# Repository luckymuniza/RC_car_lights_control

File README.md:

# RC Car Lights Control

Lighting controller for a large-scale RC truck. An RP2040 board sits between the
FlySky receiver and a **MFC-03** multi-function unit, reads the receiver's **iBUS**
stream directly, and drives the vehicle's LED lighting from it — while still letting the
MFC-03 keep control of the things it does best (sound, engine start-up sequence,
turn-signal timing, brake detection).

The MCU is both a *consumer* of the MFC-03 (it watches the MFC's own light and
turn-signal outputs) and a *producer* for it (it synthesises a servo signal into the MFC's
light channel so the MFC's internal "lights on" state stays in sync).

```
FlySky FS-i6X  ──2.4GHz──►  FS-iA6B RX ──┬── iBUS (UART, 115200) ──► RP2040 ──► LED outputs
                                          │                            ▲  │
                                          └── (channels) ──► MFC-03 ───┘  │
                                                                ▲          │
                                                                └──────────┘
                                                            synthesised servo signal
```

## Repository layout

| Path | Contents |
| --- | --- |
| `FW/` | Firmware — C, Raspberry Pi Pico SDK ≥ 2.1.0 |
| `HW/rccarcontrol/` | KiCad 9 project: schematic, PCB, gerbers, DRC report |
| `doc/` | MFC-03 manual, FS-i6X manual, output mapping spreadsheet, wiring manual |
| `sim/` | Multisim analog simulation (`Design1.ms14`) |

## Hardware

The board is built around a **USB-C RP2040 "Pico C" module** (`HW/.../rccarcontrol.kicad_sch`,
symbol `Pico_type_c`). Note this is *not* pin-compatible with a genuine Raspberry Pi Pico:
the module breaks out **GPIO29 on pad 35** and **GPIO23 on pad 37**, where a stock Pico has
`ADC_VREF` and `3V3_EN`. The firmware drives both of those pins, so it will not run
correctly on a stock Pico without remapping `FRONT_RAMP_LIGHT_OUT_PIN` and
`TURN_R_FRONT_OUT_PIN`.

Interfacing:

- **Inputs from the MFC-03** go through `EL3H7` optocouplers (U2–U8), so they are
  **active-low** and the firmware enables internal pull-ups on all of them.
- **Outputs** drive `IRLML0030` N-MOSFETs. Solder jumpers `JP3`–`JP7` select `+7V2_LED` or
  `+5V_LED` per LED group; `JP1`/`JP2` bring the receiver / external supply onto `+5V`.
- **Reverse light** (`REVERSE_LIGHT_IN`, opto U1) is wired straight to Q1/Q2 in hardware and
  never reaches the MCU — there is intentionally no firmware for it.

### Pin map

Verified against the PCB netlist. "Pad" is the module pad number.

**Outputs**

| GPIO | Pad | Net | Firmware | Type |
| --- | --- | --- | --- | --- |
| 0 | 1 | `LED_POWER` | `lights.c` | digital — master LED supply gate |
| 1 | 2 | `LOW_BEAM_OUT` | `lights.c` | digital |
| 2 | 4 | `HIGH_BEAM_OUT` | `lights.c` | digital |
| 3 | 5 | `FOG_LIGHT_OUT` | `lights.c` | digital |
| 4 | 6 | `AUX_1_OUT` | `aux1.c` | PWM slice 2A, 50 Hz servo, **inverted** polarity |
| 5 | 7 | `AUX_2_OUT` | `main.c` | digital — toggled every loop pass (loop-rate test point) |
| 6 | 9 | `TURN_R_PWM_OUT` | `turn_light.c` | PWM slice 3A, 2 kHz |
| 7 | 10 | `TURN_L_PWM_OUT` | `turn_light.c` | PWM slice 3B, 2 kHz |
| 8 | 11 | `TURN_L_FRONT_OUT` | `turn_light.c` | digital — short front-indicator pulse |
| 9 | 12 | `SEARCH_LIGHT_OUT` | `lights.c` | digital |
| 10 | 14 | `REAR_LIGHT_PWM_OUT` | `rear_light.c` | PWM slice 5A, 500 Hz |
| 11 | 15 | `SIDE_LIGHT_1_OUT` | `lights.c` | digital |
| 12 | 16 | `SIDE_LIGHT_2_OUT` | `lights.c` | digital |
| 13 | 17 | `RX_PWM_OUT` | `to_mfc.c` | PWM slice 6B, 50 Hz servo → MFC light channel |
| 14 | 19 | `BEACON_SMALL_PWM_OUT` | `beacons.c` | PWM slice 7A, 50 Hz servo |
| 15 | 20 | `BEACON_BIG_PWM_OUT` | `beacons.c` | PWM slice 7B, 50 Hz servo |
| 23 | 37 | `TURN_R_FRONT_OUT` | `turn_light.c` | digital |
| 25 | — | on-board LED | `main.c` | boot-blink only |
| 27 | 32 | `DAY_LIGHT_OUT` | `lights.c` | digital — on permanently after init |
| 28 | 34 | `POSITION_LIGHT_OUT` | `lights.c` | digital |
| 29 | 35 | `FRONT_RAMP_OUT` | `lights.c` | digital |

**Inputs** (all pulled up, active low)

| GPIO | Pad | Net | Firmware | Purpose |
| --- | --- | --- | --- | --- |
| 16 | 21 | `TURN_R_IN` | `turn_light.c` | MFC right indicator |
| 17 | 22 | `LIGHT_0_IN` | `lights.c` | configured, **not read** |
| 18 | 24 | `LIGHT_1_IN` | `lights.c` | MFC light state + start-up flash pattern |
| 19 | 25 | `LIGHT_2_IN` | `lights.c` | configured, **not read** |
| 20 | 26 | `LIGHT_3_IN` | `lights.c` | configured, **not read** |
| 21 | 27 | `RX_SBUS_IN` | `ibus.c` | UART1 RX — iBUS, 115200 8N1 |
| 22 | 29 | `TURN_L_IN` | `turn_light.c` | MFC left indicator |
| 26 | 31 | `REAR_BRAKE_IN` | `rear_light.c` | ADC0 — MFC rear/brake light level |

### Transmitter channel map

From `FW/ibus.h` (`ibus_channel`), 1-based as shown on the FS-i6X:

| Ch | Name | Used by |
| --- | --- | --- |
| 1 | Steering | — (passes to MFC directly) |
| 2 | MFC light channel | `to_mfc.c`, `aux1.c` |
| 3 | Throttle | — |
| 4 | Throttle X | — |
| 5 | Mode switch | `aux1.c` |
| 6 | Beacon switch | `beacons.c` |
| 7 | Gear switch | — |
| 8 | Light switch | `lights.c` |
| 9 / 10 | Pot A / Pot B | — |

Channels 1, 3, 4, 7 and the pots are declared but not consumed by the firmware.

## Firmware

### Structure

Cooperative, non-blocking super-loop. Every module exposes `*_init()` (called once) and
`*_service()` (called every pass, returns immediately). No RTOS, no blocking delays after
start-up, no dynamic allocation. All timing uses `time_us_32()` deadlines compared as
signed differences, so 32-bit wrap is handled correctly.

| Module | Responsibility |
| --- | --- |
| `main.c` | Boot blink, init order, super-loop |
| `ibus.c` | iBUS frame decoding — the only interrupt-driven part |
| `lights.c` | Light-state machine, side lights, MFC light-state sync, start-up flash replay |
| `turn_light.c` | Indicator soft fade-in / fade-out driven by MFC edges |
| `rear_light.c` | Tail / brake light PWM, ADC brake detection |
| `beacons.c` | Rotating beacons, fog + search light, beacon configuration mode |
| `to_mfc.c` | Synthesised servo output back into the MFC light channel |
| `aux1.c` | Diverts the light channel to an auxiliary servo output (crane) |
| `switch.h` | Shared 3-position-switch state machine constants |

### iBUS decoder

`ibus.c` decodes the standard 32-byte FlySky iBUS servo frame:

```
0x20 0x40 <14 × uint16 LE channel values> <uint16 LE checksum>
```

The checksum is validated by summing all 32 bytes and requiring `0xFFFF`. Frame
synchronisation is done by **inter-byte gap**, not by header alone: a byte arriving more
than `SBUS_NEXT_FRAME_TIMEGAP` (3 ms) after the previous one is treated as a frame start.
Frames arrive roughly every 7 ms and each takes ~2.7 ms, so the gap is unambiguous.

The ISR writes into `channel_data`; `ibus_service()` copies it to `channel_data_saved`
with interrupts disabled, and `ibus_get_channel()` reads only the snapshot.

### Light state machine (`lights.c`)

Channel 8 acts as a momentary 3-position switch. Short pull **up** steps forward, holding
up for >1 s steps back:

```
OFF ──► POSITION ──► LOW_BEAM ──► HIGH_BEAM ──► RAMP
    ◄──          ◄──          ◄──           ◄──          (hold >1 s)
```

Pushing **down** flashes the front ramp light for as long as it is held.

Side lights (`SIDE_LIGHT_1/2`) have their own state: off, on with the position lights, a
double-flash alternating beacon pattern (when the rotating beacons are on), or a slow
0.5 s blink to indicate beacon-configuration mode.

### MFC light-state sync

The MFC-03 beeps when the engine is switched off with its lights still on, so its internal
state must track the real one. `update_lights_in_mfc()` compares `l_state` against
`LIGHT_1_IN` and, when they disagree, asks `to_mfc.c` to emit one 100 ms pulse train on the
synthesised light channel — the equivalent of one stick flick. It repeats every 0.5 s until
the states match.

### Start-up flash replay

On engine start the MFC-03 flashes its light output rapidly. `detect_starting_seq()`
detects this (edges closer than 25 ms apart), records the on/off durations into a 64-entry
ring buffer — duration in bits 0–14, level in bit 15 — and replays them onto `LED_POWER`
so the real headlights flicker in step with the MFC's simulated start-up. While the replay
is active, MFC light-state sync is suspended.

### Turn signals

The MFC drives the blink timing; the firmware only reshapes it. On each falling edge of
`TURN_L_IN` / `TURN_R_IN` it pulses the front indicator hard for 100 ms and simultaneously
ramps the PWM channel up (100 counts / 10 ms), holds at full for 100 ms, then ramps down
(50 counts / 7.5 ms) — roughly a 600 ms incandescent-style fade. Re-triggering is ignored
while a fade is still running.

### Rear / brake light

`REAR_BRAKE_IN` is sampled on ADC0 through a 32-sample moving average. Below
`REAR_LIGHT_BRAKE_LEVEL` the tail light PWM goes to full (brake); otherwise it follows the
main light state at 25 % duty, or off.

### Beacons

Two servo-protocol beacon outputs, driven as if by a stick:

- **Short pull up** — both beacons on, side lights switch to the alternating flash pattern.
- **Hold up >1 s** — both off. The small beacon has to be cycled through all four of its
  internal modes to reach off, which `beacon_small_off()` does with eight 50 ms pulses.
- **Hold up >5 s** — enter configuration mode: big beacon on, side lights blink slowly. In
  config, short up = next mode, short down = next brightness, hold up >5 s = exit.
- **Short pull down** — cycles the rear search light and the fog light. Hold down >1 s
  turns both off. The fog light only comes on if the main lights are on.

### Auxiliary output

When channel 5 is above 1800, `aux1.c` mirrors the channel-2 value onto `AUX_1_OUT`
(inverted polarity) for a crane servo, and tells `to_mfc.c` to park the MFC light channel at
centre so the MFC ignores it.

## Building

Requires the Raspberry Pi Pico SDK **2.1.0 or later**, `arm-none-eabi-gcc`, CMake ≥ 3.12
and `picotool`.

```sh
export PICO_SDK_PATH=/path/to/pico-sdk
cd FW
cmake -B build -DCMAKE_BUILD_TYPE=Debug
cmake --build build
```

Output is `build/car_lighting.uf2` (plus `.elf`, `.bin`, `.hex`, `.map`). The build prints
memory usage and a section size summary.

`CMakeLists.txt` hardcodes `picotool_DIR` to a local absolute path; override it with
`-Dpicotool_DIR=...` or edit it if picotool lives elsewhere. `stdio` over both USB and UART
is disabled — GPIO0/GPIO1 are used as light outputs, so UART0 is unavailable. To get printf
debugging you must free those pins first.

## Flashing

Hold `BOOTSEL` while plugging the board in and copy the `.uf2` to the `RPI-RP2` drive.

`FW/up.bat` automates this on Windows: it pokes the USB CDC port at 1200 baud to force the
board into BOOTSEL, finds the `RPI-RP2` volume and copies the image. It references helper
tools under `f:\_Work\_Programing\rpi\` and expects the artefact in
`cmake-build-debug-system-arm\`, so the paths need adjusting for the current build
directory before it will work.

## Known limitations

- **No receiver failsafe.** `ibus_get_channel()` returns the last valid frame forever. If
  the link drops, the lighting freezes in its last state and the synthesised MFC channel
  keeps repeating a stale value.
- **Boot blocks on iBUS.** `main()` spins in `while (!ibus_data_valid())` before any
  outputs are initialised, so with no receiver signal the board never leaves start-up.
- **No watchdog.**
- `LIGHT_0_IN`, `LIGHT_2_IN`, `LIGHT_3_IN` are wired and configured but unused.

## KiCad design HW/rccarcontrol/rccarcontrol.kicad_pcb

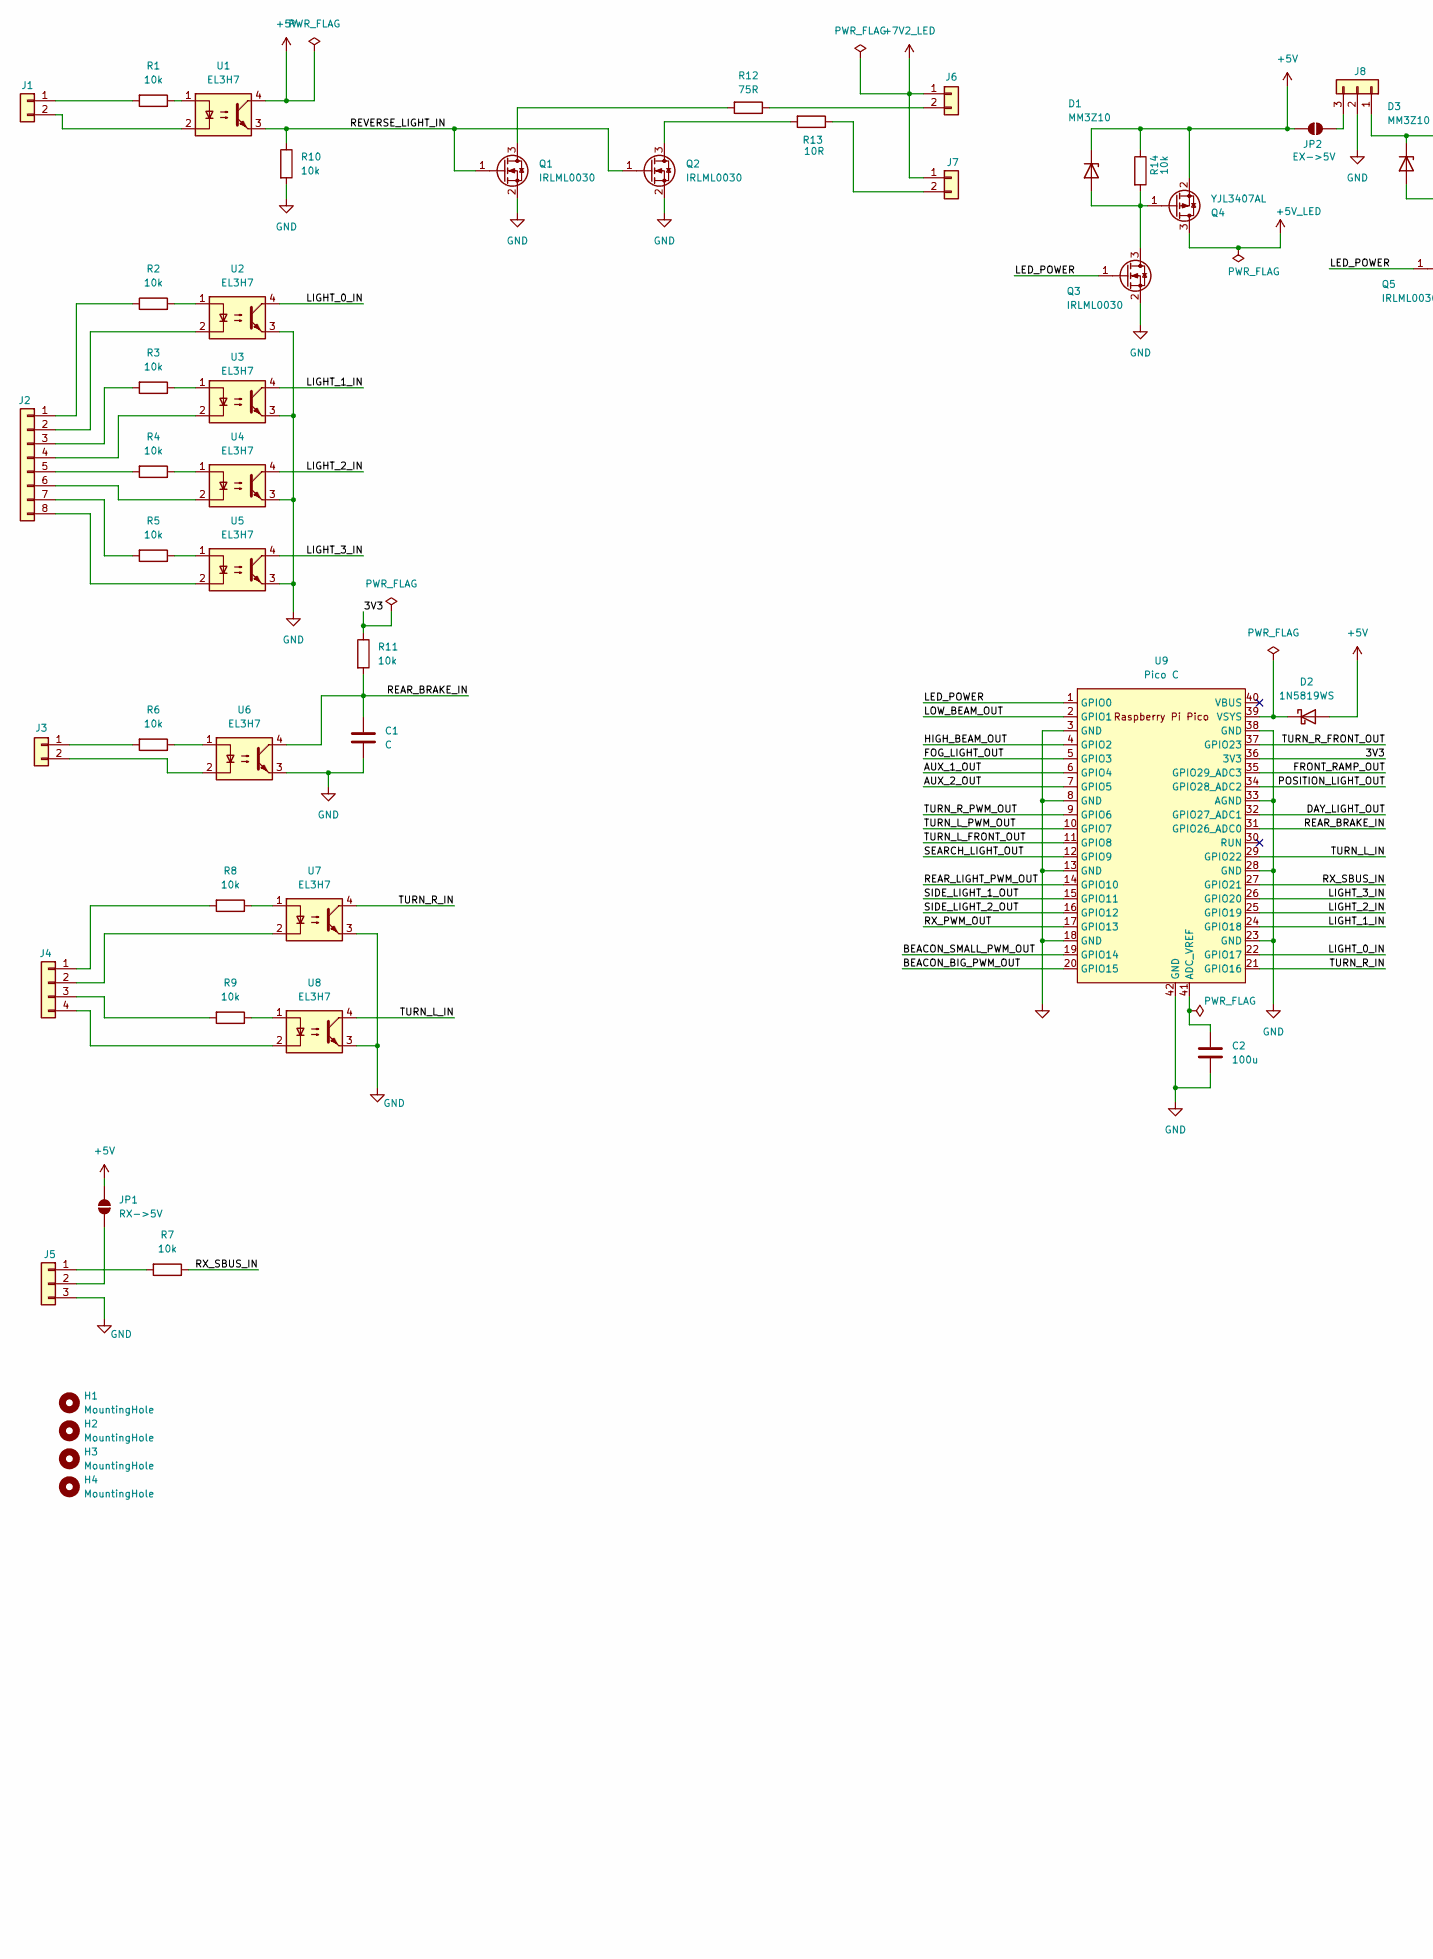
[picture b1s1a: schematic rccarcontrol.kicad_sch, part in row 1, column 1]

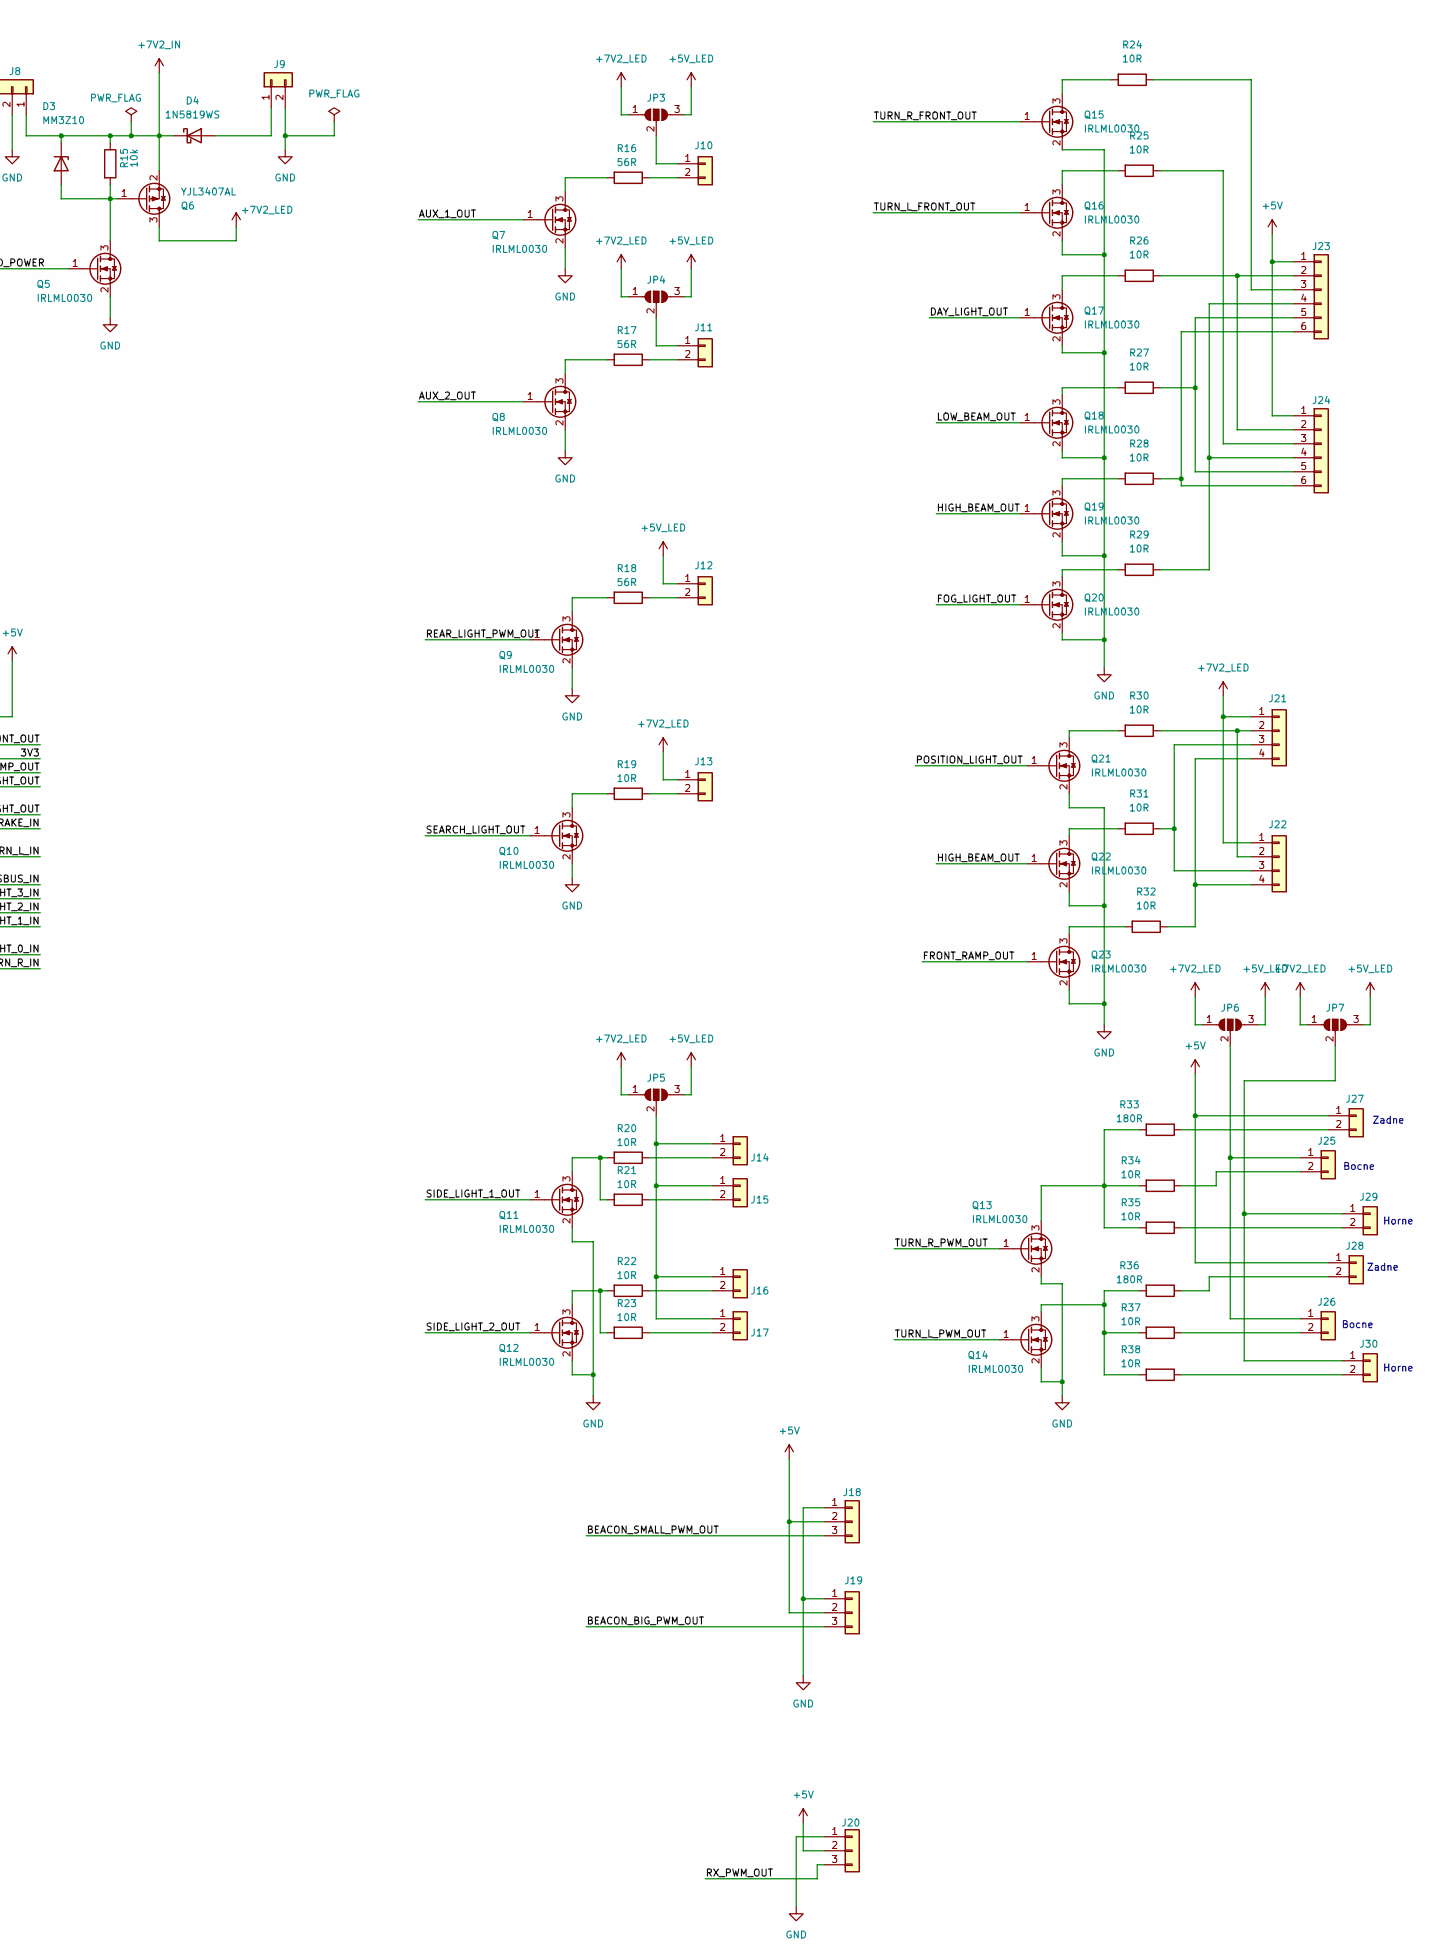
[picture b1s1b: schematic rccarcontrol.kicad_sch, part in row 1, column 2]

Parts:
C1: C; C_1206_3216Metric_Pad1.33x1.80mm_HandSolder
C2: 100u; C_1206_3216Metric_Pad1.33x1.80mm_HandSolder
D1, D3: MM3Z10; D_SOD-323F
D2, D4: 1N5819WS; D_SOD-123
H1, H2, H3, H4: MountingHole; MountingHole_2mm
J1, J3, J6, J7, J9, J10, J11, J12, J13, J14, J15, J16, J17, J25, J26, J27, J28, J29, J30: Conn_01x02; JST_PH_B2B-PH-K_1x02_P2.00mm_Vertical
J2: Conn_01x08; JST_PH_B8B-PH-K_1x08_P2.00mm_Vertical
J4, J21, J22: Conn_01x04; JST_PH_B4B-PH-K_1x04_P2.00mm_Vertical
J5, J8, J18, J19, J20: Conn_01x03; JST_PH_B3B-PH-K_1x03_P2.00mm_Vertical
J23, J24: Conn_01x06; JST_PH_B6B-PH-K_1x06_P2.00mm_Vertical
JP1: RX->5V; SolderJumper-2_P1.3mm_Open_RoundedPad1.0x1.5mm
JP2: EX->5V; SolderJumper-2_P1.3mm_Open_RoundedPad1.0x1.5mm
JP3, JP4, JP5, JP6, JP7: SolderJumper_3_Open; SolderJumper-3_P1.3mm_Open_RoundedPad1.0x1.5mm_NumberLabels
Q1, Q2, Q3, Q5, Q7, Q8, Q9, Q10, Q11, Q12, Q13, Q14, Q15, Q16, Q17, Q18, Q19, Q20, Q21, Q22, Q23: IRLML0030; SOT-23-3
Q4, Q6: YJL3407AL; SOT-23-3
R1, R2, R3, R4, R5, R6, R7, R8, R9, R10, R11, R14, R15: 10k; R_0805_2012Metric_Pad1.20x1.40mm_HandSolder
R12: 75R; R_0805_2012Metric_Pad1.20x1.40mm_HandSolder
R13, R19, R20, R21, R22, R23, R24, R25, R26, R27, R28, R29, R30, R31, R32, R34, R35, R37, R38: 10R; R_0805_2012Metric_Pad1.20x1.40mm_HandSolder
R16, R17, R18: 56R; R_0805_2012Metric_Pad1.20x1.40mm_HandSolder
R33, R36: 180R; R_0805_2012Metric_Pad1.20x1.40mm_HandSolder
U1, U2, U3, U4, U5, U6, U7, U8: EL3H7; SOP-4_4.4x2.6mm_P1.27mm
U9: Pico C; RPi_Pico_type_c_SMD_TH

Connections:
+5V: D1.1 (K), D2.2 (A), J18.2, J19.2, J20.2, J23.1, J24.1, J27.1, J28.1, JP1.2 (B), JP2.2 (B), Q4.2 (S), R14.1, U1.4
+5V_LED: J12.1, JP3.3 (B), JP4.3 (B), JP5.3 (B), JP6.3 (B), JP7.3 (B), Q4.3 (D)
+7V2_IN: D3.1 (K), D4.1 (K), J8.1, Q6.2 (S), R15.1
+7V2_LED: J6.1, J7.1, J13.1, J21.1, J22.1, JP3.1 (A), JP4.1 (A), JP5.1 (A), JP6.1 (A), JP7.1 (A), Q6.3 (D)
/3V3: R11.1, U9.36 (3V3)
/AUX_1_OUT: Q7.1 (G), U9.6 (GPIO4)
/AUX_2_OUT: Q8.1 (G), U9.7 (GPIO5)
/BEACON_BIG_PWM_OUT: J19.3, U9.20 (GPIO15)
/BEACON_SMALL_PWM_OUT: J18.3, U9.19 (GPIO14)
/DAY_LIGHT_OUT: Q17.1 (G), U9.32 (GPIO27_ADC1)
/FOG_LIGHT_OUT: Q20.1 (G), U9.5 (GPIO3)
/FRONT_RAMP_OUT: Q23.1 (G), U9.35 (GPIO29_ADC3)
/HIGH_BEAM_OUT: Q19.1 (G), Q22.1 (G), U9.4 (GPIO2)
/LED_POWER: Q3.1 (G), Q5.1 (G), U9.1 (GPIO0)
/LIGHT_0_IN: U2.4, U9.22 (GPIO17)
/LIGHT_1_IN: U3.4, U9.24 (GPIO18)
/LIGHT_2_IN: U4.4, U9.25 (GPIO19)
/LIGHT_3_IN: U5.4, U9.26 (GPIO20)
/LOW_BEAM_OUT: Q18.1 (G), U9.2 (GPIO1)
/POSITION_LIGHT_OUT: Q21.1 (G), U9.34 (GPIO28_ADC2)
/REAR_BRAKE_IN: C1.2, R11.2, U6.4, U9.31 (GPIO26_ADC0)
/REAR_LIGHT_PWM_OUT: Q9.1 (G), U9.14 (GPIO10)
/REVERSE_LIGHT_IN: Q1.1 (G), Q2.1 (G), R10.1, U1.3
/RX_PWM_OUT: J20.3, U9.17 (GPIO13)
/RX_SBUS_IN: R7.1, U9.27 (GPIO21)
/SEARCH_LIGHT_OUT: Q10.1 (G), U9.12 (GPIO9)
/SIDE_LIGHT_1_OUT: Q11.1 (G), U9.15 (GPIO11)
/SIDE_LIGHT_2_OUT: Q12.1 (G), U9.16 (GPIO12)
/TURN_L_FRONT_OUT: Q16.1 (G), U9.11 (GPIO8)
/TURN_L_IN: U8.4, U9.29 (GPIO22)
/TURN_L_PWM_OUT: Q14.1 (G), U9.10 (GPIO7)
/TURN_R_FRONT_OUT: Q15.1 (G), U9.37 (GPIO23)
/TURN_R_IN: U7.4, U9.21 (GPIO16)
/TURN_R_PWM_OUT: Q13.1 (G), U9.9 (GPIO6)
GND: C1.1, C2.1, J5.3, J8.2, J9.2, J18.1, J19.1, J20.1, Q1.2 (S), Q2.2 (S), Q3.2 (S), Q5.2 (S), Q7.2 (S), Q8.2 (S), Q9.2 (S), Q10.2 (S), Q11.2 (S), Q12.2 (S), Q13.2 (S), Q14.2 (S), Q15.2 (S), Q16.2 (S), Q17.2 (S), Q18.2 (S), Q19.2 (S), Q20.2 (S), Q21.2 (S), Q22.2 (S), Q23.2 (S), R10.2, U2.3, U3.3, U4.3, U5.3, U6.3, U7.3, U8.3, U9.3 (GND), U9.8 (GND), U9.13 (GND), U9.18 (GND), U9.23 (GND), U9.28 (GND), U9.33 (AGND), U9.38 (GND), U9.42 (GND)
unnamed: D1.2 (A), Q3.3 (D), Q4.1 (G), R14.2
unnamed: D2.1 (K), U9.39 (VSYS)
unnamed: D3.2 (A), Q5.3 (D), Q6.1 (G), R15.2
unnamed: D4.2 (A), J9.1
unnamed: J1.1, R1.2
unnamed: J1.2, U1.2
unnamed: J2.1, R2.1
unnamed: J2.2, U2.2
unnamed: J2.3, R3.2
unnamed: J2.4, U3.2
unnamed: J2.5, R4.2
unnamed: J2.6, U4.2
unnamed: J2.7, R5.2
unnamed: J2.8, U5.2
unnamed: J3.1, R6.2
unnamed: J3.2, U6.2
unnamed: J4.1, R8.2
unnamed: J4.2, U7.2
unnamed: J4.3, R9.2
unnamed: J4.4, U8.2
unnamed: J5.1, R7.2
unnamed: J5.2, JP1.1 (A)
unnamed: J6.2, R12.1
unnamed: J7.2, R13.1
unnamed: J8.3, JP2.1 (A)
unnamed: J10.1, JP3.2 (C)
unnamed: J10.2, R16.1
unnamed: J11.1, JP4.2 (C)
unnamed: J11.2, R17.1
unnamed: J12.2, R18.1
unnamed: J13.2, R19.1
unnamed: J14.1, J15.1, J16.1, J17.1, JP5.2 (C)
unnamed: J14.2, R20.1
unnamed: J15.2, R21.1
unnamed: J16.2, R22.1
unnamed: J17.2, R23.1
unnamed: J21.2, J22.2, R30.1
unnamed: J21.3, J22.3, R31.1
unnamed: J21.4, J22.4, R32.1
unnamed: J23.2, J24.2, R26.1
unnamed: J23.3, R24.1
unnamed: J23.4, J24.4, R29.1
unnamed: J23.5, J24.5, R27.1
unnamed: J23.6, J24.6, R28.1
unnamed: J24.3, R25.1
unnamed: J25.1, J26.1, JP6.2 (C)
unnamed: J25.2, R34.1
unnamed: J26.2, R37.1
unnamed: J27.2, R33.1
unnamed: J28.2, R36.1
unnamed: J29.1, J30.1, JP7.2 (C)
unnamed: J29.2, R35.1
unnamed: J30.2, R38.1
unnamed: Q1.3 (D), R12.2
unnamed: Q2.3 (D), R13.2
unnamed: Q7.3 (D), R16.2
unnamed: Q8.3 (D), R17.2
unnamed: Q9.3 (D), R18.2
unnamed: Q10.3 (D), R19.2
unnamed: Q11.3 (D), R20.2, R21.2
unnamed: Q12.3 (D), R22.2, R23.2
unnamed: Q13.3 (D), R33.2, R34.2, R35.2
unnamed: Q14.3 (D), R36.2, R37.2, R38.2
unnamed: Q15.3 (D), R24.2
unnamed: Q16.3 (D), R25.2
unnamed: Q17.3 (D), R26.2
unnamed: Q18.3 (D), R27.2
unnamed: Q19.3 (D), R28.2
unnamed: Q20.3 (D), R29.2
unnamed: Q21.3 (D), R30.2
unnamed: Q22.3 (D), R31.2
unnamed: Q23.3 (D), R32.2
unnamed: R1.1, U1.1
unnamed: R2.2, U2.1
unnamed: R3.1, U3.1
unnamed: R4.1, U4.1
unnamed: R5.1, U5.1
unnamed: R6.1, U6.1
unnamed: R8.1, U7.1
unnamed: R9.1, U8.1
unnamed: C2.2, U9.41 (ADC_VREF)

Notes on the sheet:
Horne
Zadne
Bocne

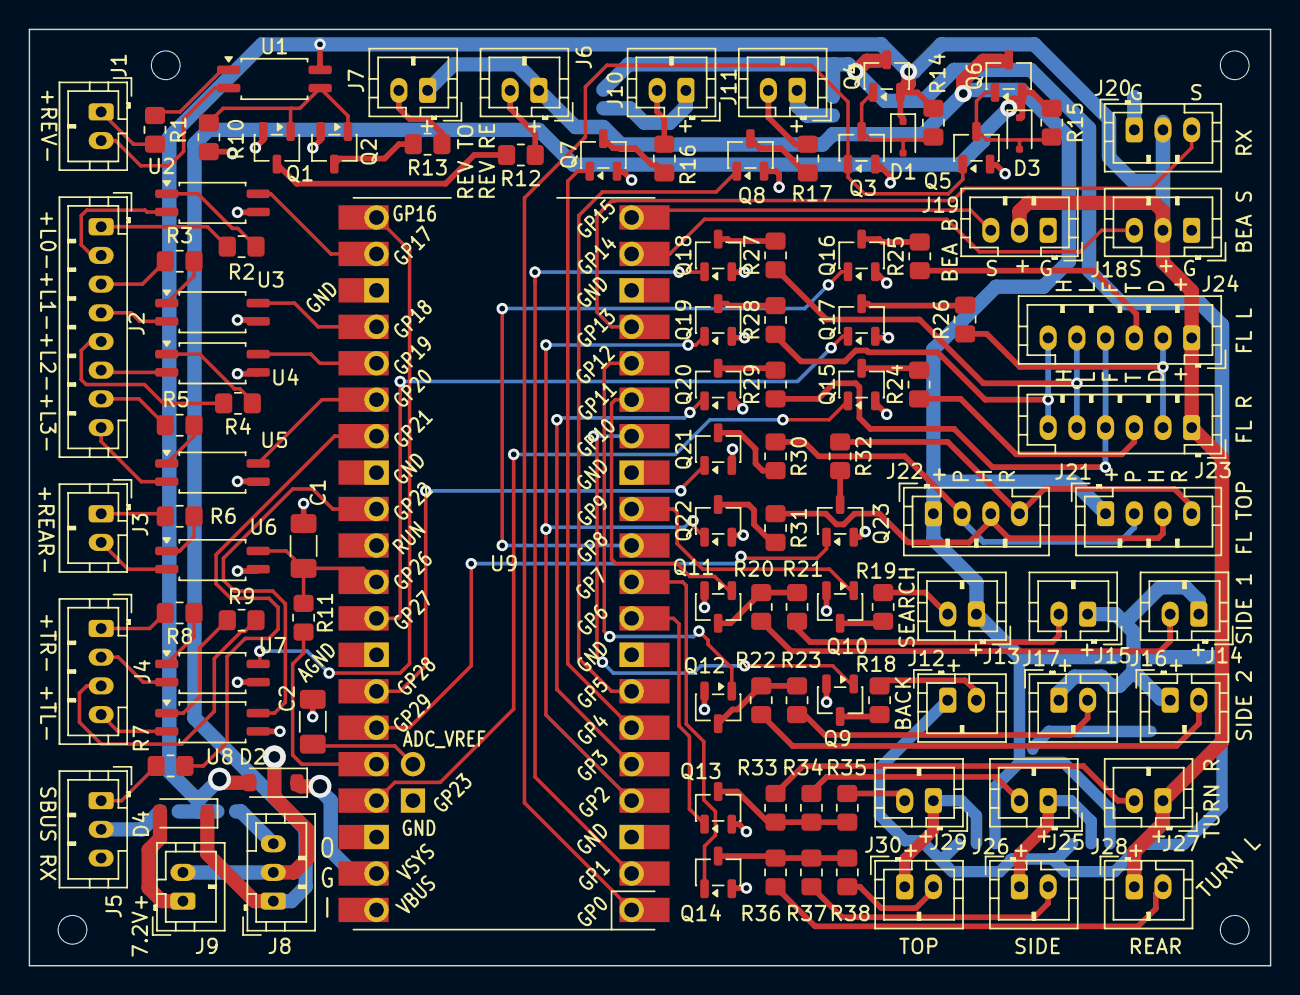
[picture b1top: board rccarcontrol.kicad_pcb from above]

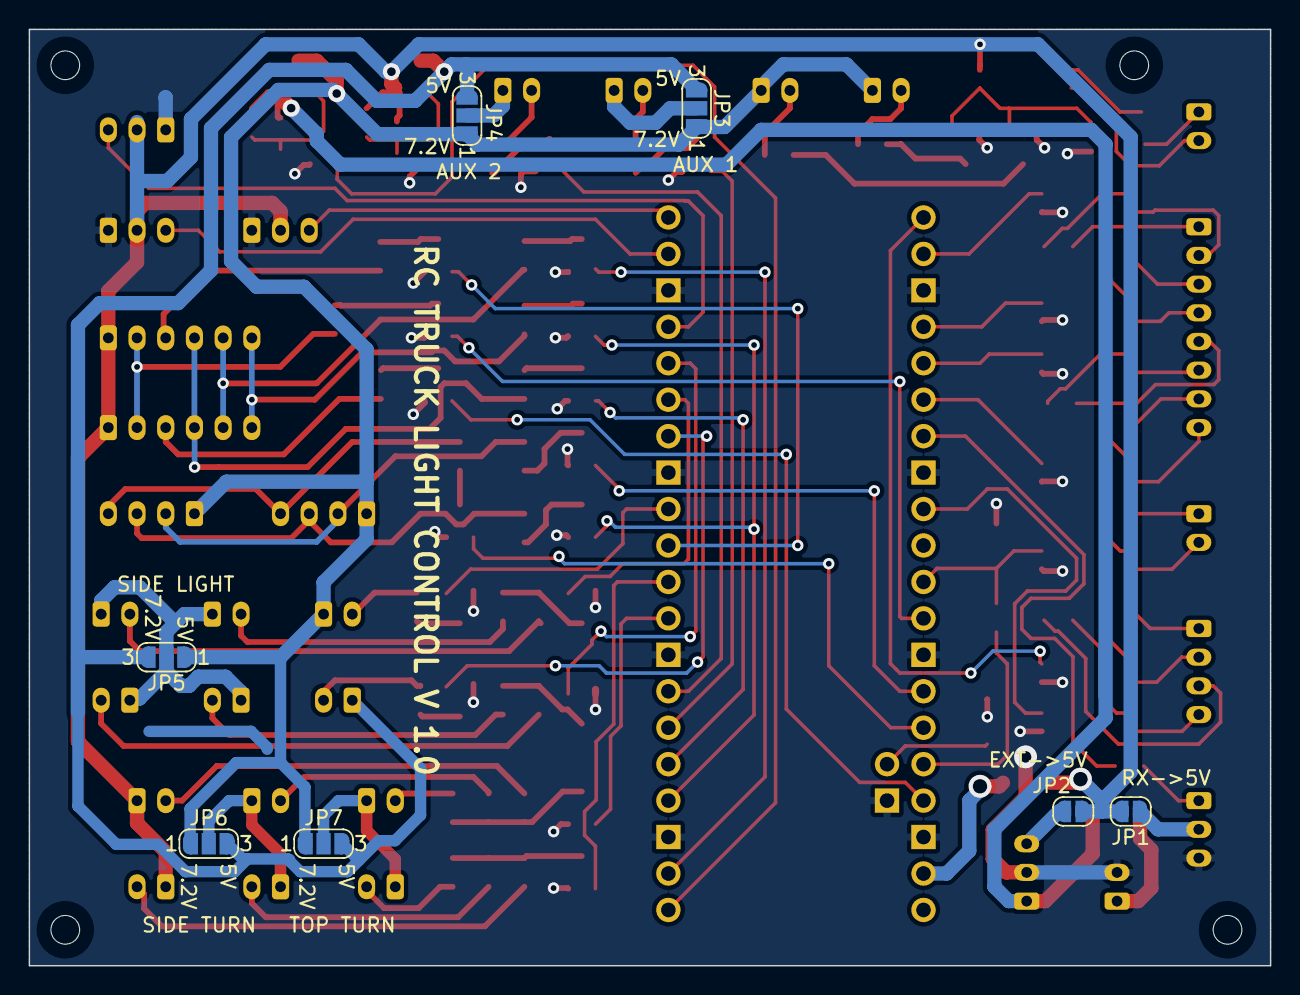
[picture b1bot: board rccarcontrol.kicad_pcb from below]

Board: 2 copper layers, 86.5 x 65.2 mm, 117 parts (7 on the bottom side), 116 nets.

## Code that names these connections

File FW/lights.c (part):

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#include "beacons.h"
#include "to_mfc.h"

#define LED_POWER_PIN 0
#define DAY_LIGHT_OUTPUT_PIN 27  //0 je stdout uart0
#define LOW_BEAM_OUT_PIN    1
#define HIGH_BEAM_OUT_PIN   2
#define FOG_LIGHT_OUT_PIN   3
#define POSITION_LIGHT_OUT_PIN    28
#define FRONT_RAMP_LIGHT_OUT_PIN    29
#define REAR_SEARCH_LIGHT_OUT_PIN 9
#define SIDE_LIGHT_1_OUT_PIN 11
#define SIDE_LIGHT_2_OUT_PIN 12

//pwm out

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static uint8_t starting_seq = 0;

void side_light_1_on (void) {
    gpio_put(SIDE_LIGHT_1_OUT_PIN, 1);
}
void side_light_1_off (void) {
    gpio_put(SIDE_LIGHT_1_OUT_PIN, 0);
}
void side_light_2_on (void) {
    gpio_put(SIDE_LIGHT_2_OUT_PIN, 1);
}
void side_light_2_off (void) {
    gpio_put(SIDE_LIGHT_2_OUT_PIN, 0);
}

void day_light_on (void) {
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}

void low_beam_on (void) {
    gpio_put(LOW_BEAM_OUT_PIN, 1);
}
void low_beam_off (void) {
    gpio_put(LOW_BEAM_OUT_PIN, 0);
}

void high_beam_on (void) {
    gpio_put(HIGH_BEAM_OUT_PIN, 1);
}
void high_beam_off (void) {
    gpio_put(HIGH_BEAM_OUT_PIN, 0);
}

void fog_light_on (void) {
    gpio_put(FOG_LIGHT_OUT_PIN, 1);
}
void fog_light_off (void) {
    gpio_put(FOG_LIGHT_OUT_PIN, 0);
}

void position_light_on (void) {
    gpio_put(POSITION_LIGHT_OUT_PIN, 1);
}
void position_light_off (void) {
    gpio_put(POSITION_LIGHT_OUT_PIN, 0);
}

void front_ramp_light_on (void) {
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    gpio_put(REAR_SEARCH_LIGHT_OUT_PIN, 0);
}

//okrem pinu led_power este aj hlavne svetla lebo tam to 5V nespina
void led_power_on (void) {
    gpio_put(LED_POWER_PIN, 1);
    if (l_state == L_STATE_LOW_BEAM) {
        low_beam_on();
    }
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

void led_power_off (void) {
    gpio_put(LED_POWER_PIN, 0);
    if (l_state == L_STATE_LOW_BEAM) {
        low_beam_off();
    }
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    //init pins
    gpio_set_function_masked(
      (1<<DAY_LIGHT_OUTPUT_PIN)
      |(1<<LED_POWER_PIN)
      |(1<<LOW_BEAM_OUT_PIN)
      |(1<<HIGH_BEAM_OUT_PIN)
      |(1<<FOG_LIGHT_OUT_PIN)
      |(1<<POSITION_LIGHT_OUT_PIN)
      |(1<<FRONT_RAMP_LIGHT_OUT_PIN)
      |(1<<REAR_SEARCH_LIGHT_OUT_PIN)
      |(1<<SIDE_LIGHT_1_OUT_PIN)
      |(1<<SIDE_LIGHT_2_OUT_PIN)
      |(1<<LIGHT_0_17_IN_PIN)
      |(1<<LIGHT_1_15_IN_PIN)
      |(1<<LIGHT_2_20_IN_PIN)
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        |(1<<LIGHT_2_20_IN_PIN)
        |(1<<LIGHT_3_13_IN_PIN));
    gpio_set_dir_out_masked(
    (1<<LED_POWER_PIN)
        |(1<<DAY_LIGHT_OUTPUT_PIN)
        |(1<<LOW_BEAM_OUT_PIN)
        |(1<<HIGH_BEAM_OUT_PIN)
        |(1<<FOG_LIGHT_OUT_PIN)
        |(1<<POSITION_LIGHT_OUT_PIN)
        |(1<<FRONT_RAMP_LIGHT_OUT_PIN)
        |(1<<REAR_SEARCH_LIGHT_OUT_PIN)
        |(1<<SIDE_LIGHT_1_OUT_PIN)
        |(1<<SIDE_LIGHT_2_OUT_PIN));

    //pullups
    gpio_set_pulls(LIGHT_0_17_IN_PIN,true,false);
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
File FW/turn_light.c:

//
// Created by all on 26. 11. 2025.
//

#include "turn_light.h"
#include "pico/stdlib.h"
#include "hardware/pwm.h"



#define TURN_L_FRONT_OUT_PIN 8   //predne smerovky pre kratky pulz
#define TURN_R_FRONT_OUT_PIN 23   //predne smerovky pre kratky pulz
#define TURN_R_PWM_OUT_PIN   6          //slice 3 A
#define TURN_L_PWM_OUT_PIN   7          //slice 3 B

#define TURN_LIGHT_R_21_IN_PIN 16
#define TURN_LIGHT_L_22_IN_PIN 22

#define TURN_LIGHT_R_MASK (1<<TURN_LIGHT_R_21_IN_PIN)
#define TURN_LIGHT_L_MASK (1<<TURN_LIGHT_L_22_IN_PIN)

#define TURN_LIGHT_PWM_INCREMENT 100
#define TURN_LIGHT_PWM_DECREMENT 50

#define TURN_LIGHT_INC_TIME_US 10000 //us
#define TURN_LIGHT_DEC_TIME_US 7500 //us
#define TURN_LIGHT_HOLD_TIME_US 100000 //us
#define TURN_LIGHT_FRONT_ON_TIME_USEC 100000
#define TURN_LIGHT_TOP_VALUE 2000

static uint pwm_slice_num_turn_light;  //smerovka PWM slice
static uint pwm_chan_num_turn_light_L;
static uint pwm_chan_num_turn_light_R;



static uint32_t turn_light_prev_state = TURN_LIGHT_L_MASK | TURN_LIGHT_R_MASK;  //L=1, R=1 - vypnute
static volatile bool turn_light_L_is_on = false;   //ze su smerovky zapnute
static volatile bool turn_light_R_is_on = false;   //ze su smerovky zapnute
static uint32_t f_turn_light_L_time;
static uint32_t f_turn_light_R_time;


//nastavit jas smeroviek 0...2000
void turn_light_L_set (uint16_t val) {
    pwm_set_chan_level(pwm_slice_num_turn_light, pwm_chan_num_turn_light_L, val);
}
void turn_light_R_set (uint16_t val) {
    pwm_set_chan_level(pwm_slice_num_turn_light, pwm_chan_num_turn_light_R, val);
}

void f_turn_light_L_on (void) {
    gpio_put(TURN_L_FRONT_OUT_PIN,true);
}
void f_turn_light_L_off (void) {
    gpio_put(TURN_L_FRONT_OUT_PIN,false);
}
void f_turn_light_R_on (void) {
    gpio_put(TURN_R_FRONT_OUT_PIN,true);
}
void f_turn_light_R_off (void) {
    gpio_put(TURN_R_FRONT_OUT_PIN,false);
}



void turn_light_init (void) {
    //init pins
    gpio_set_function_masked(
            (1<<TURN_L_FRONT_OUT_PIN)
            |(1<<TURN_R_FRONT_OUT_PIN)
            |(1<<TURN_LIGHT_R_21_IN_PIN)
            |(1<<TURN_LIGHT_L_22_IN_PIN)
            ,GPIO_FUNC_SIO);

    gpio_set_dir_in_masked(
        (1<<TURN_LIGHT_R_21_IN_PIN)
        |(1<<TURN_LIGHT_L_22_IN_PIN));

    gpio_set_dir_out_masked(
    (1<<TURN_L_FRONT_OUT_PIN)
        |(1<<TURN_R_FRONT_OUT_PIN));

    //enable pullups on turn_lights, lights inputs
    gpio_set_pulls(TURN_LIGHT_L_22_IN_PIN,true,false);
    gpio_set_pulls(TURN_LIGHT_R_21_IN_PIN,true,false);

    gpio_set_function_masked((1<<TURN_L_PWM_OUT_PIN) | (1<<TURN_R_PWM_OUT_PIN), GPIO_FUNC_PWM);

    pwm_slice_num_turn_light = pwm_gpio_to_slice_num(TURN_L_PWM_OUT_PIN); //L a R maju tu istu slice
    pwm_chan_num_turn_light_L = pwm_gpio_to_channel(TURN_L_PWM_OUT_PIN);
    pwm_chan_num_turn_light_R = pwm_gpio_to_channel(TURN_R_PWM_OUT_PIN);

    //smerovky
    //pre PWM 2000Hz: f = fsys/((1999+1) x clkdiv) = 125000000/((1999+1) x 31.25) = 2000
    //perioda = 0.5ms -> 2000
    //rozsah 0 - 0.5ms -> 0 - 2000
    //31.25 = 31 + 4/16   8bit int  + 4bit frac
    pwm_config c = pwm_get_default_config();
    pwm_config_set_clkdiv_int_frac4(&c,31,4);
    pwm_config_set_clkdiv_mode(&c, PWM_DIV_FREE_RUNNING);
    pwm_config_set_wrap(&c, 1999);
    pwm_config_set_output_polarity(&c,false,false);
    pwm_init(pwm_slice_num_turn_light, &c, true);
    turn_light_L_set(0);
    turn_light_R_set(0);
    f_turn_light_L_off();
    f_turn_light_R_off();

}

void turn_light_service (void) {
    uint32_t dt;
    static uint32_t ftL;
    static uint32_t ftR;
    static uint32_t tL;
    static uint32_t tR;
    static uint32_t valR;
    static uint32_t valL;
    static bool upL;
    static bool upR;

    //detekuje hranu a 1->0 potom necha zapnute urcity cas smerovky



    uint32_t turnlight_new_state = gpio_get_all();
    turnlight_new_state &= TURN_LIGHT_L_MASK | TURN_LIGHT_R_MASK;
     uint32_t tmp = turn_light_prev_state ^ turnlight_new_state;  //ak je zmena = tmp = 1
    tmp &= turn_light_prev_state;    //predchadzajuci stav ak je 1 tak toto je pozadadovana hrana 1->0
    turn_light_prev_state = turnlight_new_state;


    if (!turn_light_L_is_on && (tmp & TURN_LIGHT_L_MASK)) {
        //turnlight_L switched on
        turn_light_L_is_on = true;
        ftL = time_us_32() + TURN_LIGHT_FRONT_ON_TIME_USEC ;
        f_turn_light_L_on();

        valL = TURN_LIGHT_PWM_INCREMENT;
        turn_light_L_set(valL);
        tL = time_us_32() + TURN_LIGHT_INC_TIME_US;
        upL = true;
    }
    if (!turn_light_R_is_on && (tmp & TURN_LIGHT_R_MASK)) {
        //turnlight_R switched on
        turn_light_R_is_on = true;
        ftR = time_us_32() + TURN_LIGHT_FRONT_ON_TIME_USEC ;
        f_turn_light_R_on();

        valR = TURN_LIGHT_PWM_INCREMENT;
        turn_light_R_set(valR);
        tR = time_us_32() + TURN_LIGHT_INC_TIME_US;
        upR = true;
    }



    if (turn_light_L_is_on) {
        dt = (time_us_32() - ftL);
        if ((int32_t) dt >= 0) {
            f_turn_light_L_off();
        }

        dt = (time_us_32() - tL);
        if ((int32_t) dt >= 0) {
            if (upL) {
                valL += TURN_LIGHT_PWM_INCREMENT;
                turn_light_L_set(valL);
                if (valL == TURN_LIGHT_TOP_VALUE) {
                    tL += TURN_LIGHT_HOLD_TIME_US;
                    upL = false;
                }
                else {
                    tL += TURN_LIGHT_INC_TIME_US;
                }
            }
            else {
                valL -= TURN_LIGHT_PWM_DECREMENT;
                turn_light_L_set(valL);
                if (valL == 0) {
                    turn_light_L_is_on = false;
                }
                else {
                    tL += TURN_LIGHT_DEC_TIME_US;
                }
            }
        }
    }


    if (turn_light_R_is_on) {
        dt = (time_us_32() - ftR);
        if ((int32_t) dt >= 0) {
            f_turn_light_R_off();
        }

        dt = (time_us_32() - tR);
        if ((int32_t) dt >= 0) {
            if (upR) {
                valR += TURN_LIGHT_PWM_INCREMENT;
                turn_light_R_set(valR);
                if (valR == TURN_LIGHT_TOP_VALUE) {
                    tR += TURN_LIGHT_HOLD_TIME_US;
                    upR = false;
                }
                else {
                    tR += TURN_LIGHT_INC_TIME_US;
                }
            }
            else {
                valR -= TURN_LIGHT_PWM_DECREMENT;
                turn_light_R_set(valR);
                if (valR == 0) {
                    turn_light_R_is_on = false;
                }
                else {
                    tR += TURN_LIGHT_DEC_TIME_US;
                }
            }
        }
    }

}
